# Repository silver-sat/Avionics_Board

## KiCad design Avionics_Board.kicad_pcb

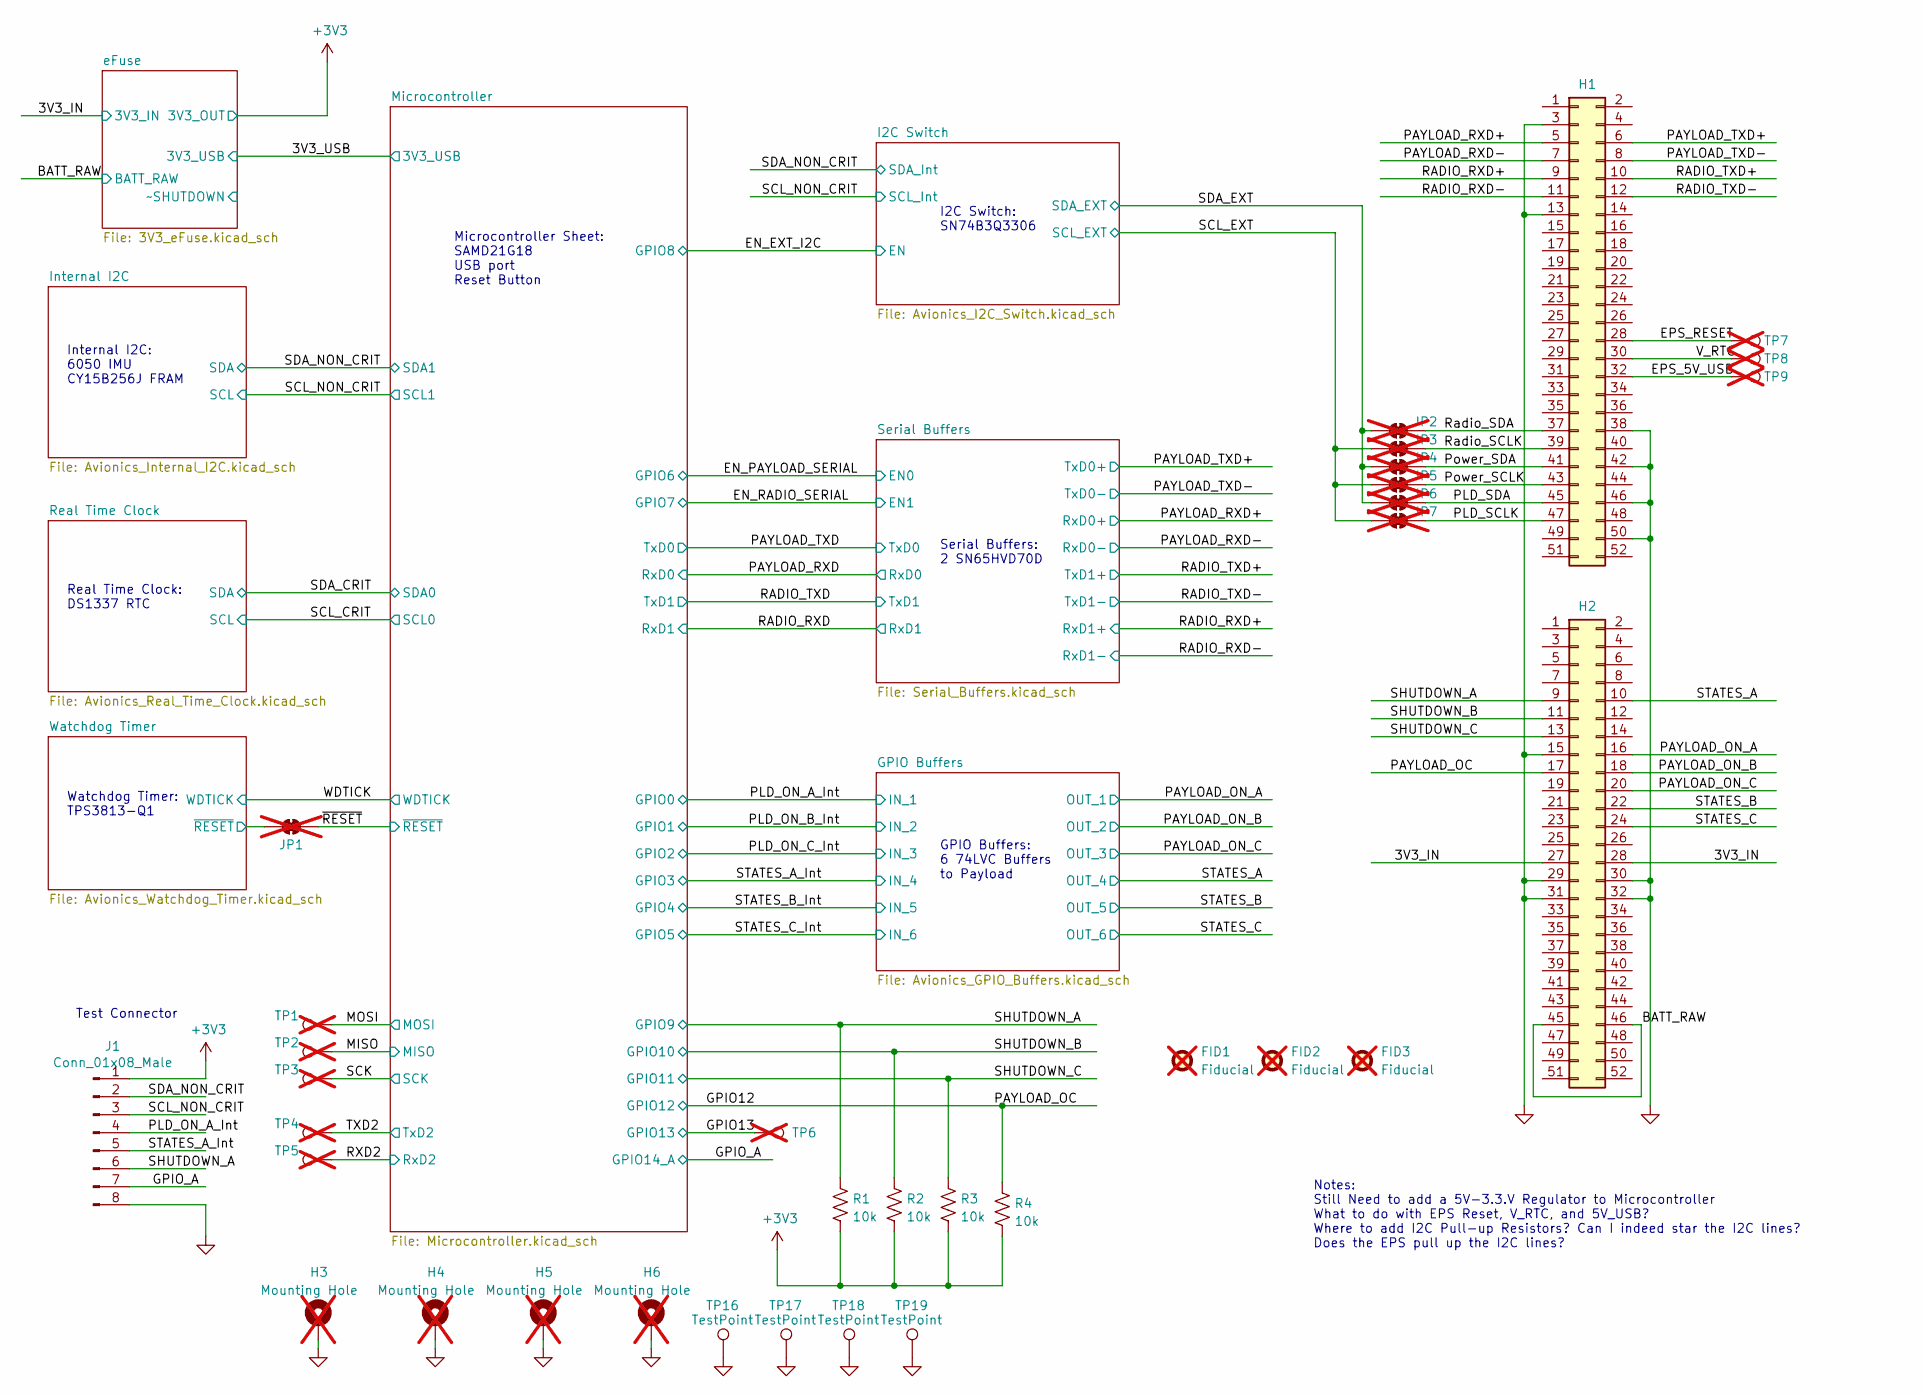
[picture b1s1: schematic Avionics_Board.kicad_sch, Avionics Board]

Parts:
FID1, FID2, FID3: Fiducial; Fiducial_1.5mm_Mask2.5mm; not fitted
H1, H2: Conn_02x26_Odd_Even; TheBus2x26; Part_Number ESQ-126-37-G-D
H3, H4, H5, H6: Mounting Hole; MountingHole_3.2mm_M3_Pad; not fitted
J1: Conn_01x08_Male; PinHeader_1x08_P2.54mm_Vertical; MPN TSW-108-26-L-S
JP1, JP2, JP3, JP4, JP5, JP6, JP7: SolderJumper_2_Bridged; SolderJumper-2_P1.3mm_Open_RoundedPad1.0x1.5mm; not fitted
R1, R2, R3, R4: 10k; R_0603_1608Metric; Part_Number ERJ-3EKF1002V
TP1: MOSI; TestPoint_Pad_2.0x2.0mm; not fitted
TP2: MISO; TestPoint_Pad_2.0x2.0mm; not fitted
TP3: SCK; TestPoint_Pad_2.0x2.0mm; not fitted
TP4: TXD2; TestPoint_Pad_2.0x2.0mm; not fitted
TP5: RXD2; TestPoint_Pad_2.0x2.0mm; not fitted
TP6: GPIO13; TestPoint_Pad_2.0x2.0mm; not fitted
TP7: EPS_RESET; TestPoint_Pad_2.0x2.0mm; not fitted
TP8: V_RTC; TestPoint_Pad_2.0x2.0mm; not fitted
TP9: EPS_5V_USB; TestPoint_Pad_2.0x2.0mm; not fitted
TP16, TP17, TP18, TP19: TestPoint; TestPoint_Keystone_5019_Minature; MPN 5019

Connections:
+3V3: J1.1, R1.2, R2.2, R3.2, R4.2; also elsewhere on the board
/3V3_IN: H2.27, H2.28; also elsewhere on the board
/BATT_RAW: H2.45, H2.46; also elsewhere on the board
/EPS_5V_USB: H1.32, TP9.1
/EPS_RESET: H1.28, TP7.1
/GPIO12: H2.17, R4.1; also elsewhere on the board
/GPIO13: TP6.1; also elsewhere on the board
/GPIO_A: J1.7; also elsewhere on the board
/MISO: TP2.1; also elsewhere on the board
/MOSI: TP1.1; also elsewhere on the board
/PAYLOAD_ON_A: H2.16; also elsewhere on the board
/PAYLOAD_ON_B: H2.18; also elsewhere on the board
/PAYLOAD_ON_C: H2.20; also elsewhere on the board
/PAYLOAD_RXD+: H1.5; also elsewhere on the board
/PAYLOAD_RXD-: H1.7; also elsewhere on the board
/PAYLOAD_TXD+: H1.6; also elsewhere on the board
/PAYLOAD_TXD-: H1.8; also elsewhere on the board
/PLD_ON_A_Int: J1.4; also elsewhere on the board
/PLD_SCLK: H1.47, JP7.2 (B)
/PLD_SDA: H1.45, JP6.2 (B)
/Power_SCLK: H1.43, JP5.2 (B)
/Power_SDA: H1.41, JP4.2 (B)
/RADIO_RXD+: H1.9; also elsewhere on the board
/RADIO_RXD-: H1.11; also elsewhere on the board
/RADIO_TXD+: H1.10; also elsewhere on the board
/RADIO_TXD-: H1.12; also elsewhere on the board
/RXD2: TP5.1; also elsewhere on the board
/Radio_SCLK: H1.39, JP3.2 (B)
/Radio_SDA: H1.37, JP2.2 (B)
/SCK: TP3.1; also elsewhere on the board
/SCL_EXT: JP3.1 (A), JP5.1 (A), JP7.1 (A); also elsewhere on the board
/SCL_NON_CRIT: J1.3; also elsewhere on the board
/SDA_EXT: JP2.1 (A), JP4.1 (A), JP6.1 (A); also elsewhere on the board
/SDA_NON_CRIT: J1.2; also elsewhere on the board
/SHUTDOWN_A: H2.9, J1.6, R1.1; also elsewhere on the board
/SHUTDOWN_B: H2.11, R2.1; also elsewhere on the board
/SHUTDOWN_C: H2.13, R3.1; also elsewhere on the board
/STATES_A: H2.10; also elsewhere on the board
/STATES_A_Int: J1.5; also elsewhere on the board
/STATES_B: H2.22; also elsewhere on the board
/STATES_C: H2.24; also elsewhere on the board
/TXD2: TP4.1; also elsewhere on the board
/V_RTC: H1.30, TP8.1
/Watchdog Timer/~RESET: JP1.1 (A); also elsewhere on the board
/~RESET: JP1.2 (B); also elsewhere on the board
GND: H1.3, H1.13, H1.38, H1.42, H1.46, H1.50, H2.15, H2.29, H2.30, H2.31, H2.32, H3.1, H4.1, H5.1, H6.1, J1.8, TP16.1, TP17.1, TP18.1, TP19.1; also elsewhere on the board

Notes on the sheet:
GPIO Buffers: 6 74LVC Buffers to Payload
Serial Buffers: 2 SN65HVD70D
Watchdog Timer: TPS3813-Q1
Real Time Clock: DS1337 RTC
Microcontroller Sheet: SAMD21G18 USB port Reset Button
Notes: Still Need to add a 5V-3.3.V Regulator to Microcontroller What to do with EPS Reset, V_RTC, and 5V_USB? Where to add I2C Pull-up Resistors? Can I indeed star the I2C lines? Does the EPS pull up the I2C lines?
Internal I2C: 6050 IMU CY15B256J FRAM
I2C Switch: SN74B3Q3306
Test Connector

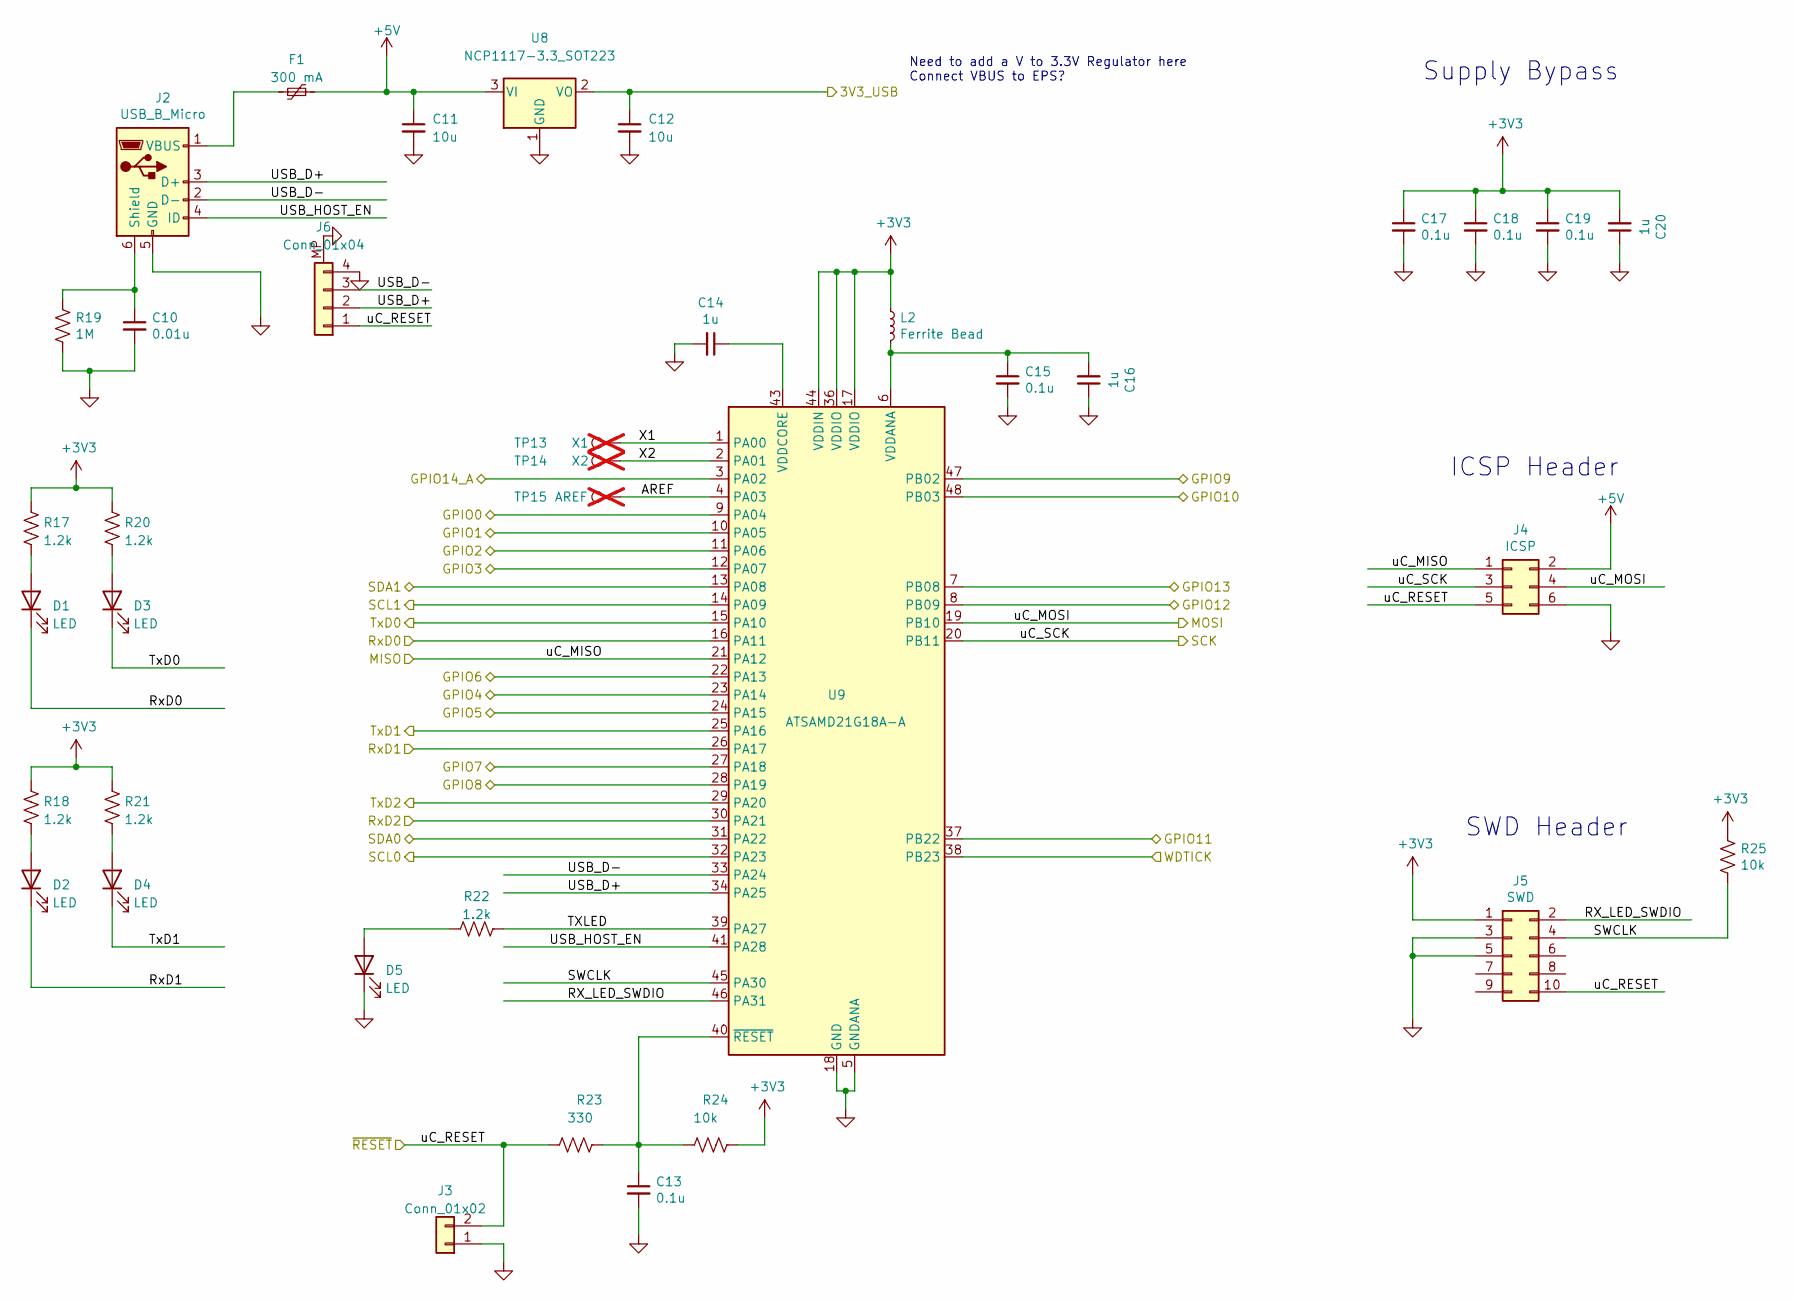
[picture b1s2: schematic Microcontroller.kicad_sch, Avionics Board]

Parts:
C10: 0.01u; C_0603_1608Metric; Part_Number 06035C472K4Z2A
C11, C12: 10u; C_2220_5650Metric_Pad1.97x5.40mm_HandSolder; Part_Number 22205C106K4Z4A
C13, C15, C17, C18, C19: 0.1u; C_0603_1608Metric; Part_Number 06035C104K4Z2A
C14, C16, C20: 1u; C_1206_3216Metric; Part_Number 12065C105M4Z2A
D1, D2, D3, D4, D5: LED; LED_0603_1608Metric; MPN CSL0903UT1C
F1: 300 mA; Fuse_0805_2012Metric; Part_Number PICOASMDC012S-2
J2: USB_B_Micro; USB_Micro-B_Molex-105017-0001; Part_Number 105017-0001
J3: Conn_01x02; PinHeader_1x02_P2.54mm_Vertical; MPN TSW-102-26-L-S
J4: ICSP; PinHeader_2x03_P2.54mm_Vertical; MPN MTSW-103-06-G-D-110
J5: SWD; PinHeader_2x05_P1.27mm_Vertical_SMD; Part_Number 4048
J6: Conn_01x04; Molex_PicoBlade_53261-0471_1x04-1MP_P1.25mm_Horizontal; MPN 53261-0471
L2: Ferrite Bead; L_0603_1608Metric; Part_Number BLM18SP102SH1D
R17, R18, R20, R21, R22: 1.2k; R_0603_1608Metric; Part_Number ERJ-3EKF9310V
R19: 1M; R_0603_1608Metric; Part_Number ERJ-3EKF1004V
R23: 330; R_0603_1608Metric; Part_Number ERJ-3EKF3300V
R24, R25: 10k; R_0603_1608Metric; Part_Number ERJ-3EKF1002V
TP13: X1; TestPoint_Pad_2.0x2.0mm; not fitted
TP14: X2; TestPoint_Pad_2.0x2.0mm; not fitted
TP15: AREF; TestPoint_Pad_2.0x2.0mm; not fitted
U8: NCP1117-3.3_SOT223; SOT-223-3_TabPin2; Part_Number NCP1117
U9: ATSAMD21G18A-A; TQFP-48_7x7mm_P0.5mm; Part_Number ATSAMD21G18A-AF

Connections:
+3V3: C17.1, C18.1, C19.1, C20.2, J5.1, L2.1, R17.1, R18.1, R20.1, R21.1, R24.1, R25.1, U9.17 (VDDIO), U9.36 (VDDIO), U9.44 (VDDIN); also elsewhere on the board
+5V: C11.1, F1.2, J4.2, U8.3 (VI)
/3V3_USB: C12.1, U8.2 (VO); also elsewhere on the board
/EN_EXT_I2C: U9.28 (PA19); also elsewhere on the board
/EN_PAYLOAD_SERIAL: U9.22 (PA13); also elsewhere on the board
/EN_RADIO_SERIAL: U9.27 (PA18); also elsewhere on the board
/GPIO12: U9.8 (PB09); also elsewhere on the board
/GPIO13: U9.7 (PB08); also elsewhere on the board
/GPIO_A: U9.3 (PA02); also elsewhere on the board
/MISO: J4.1, U9.21 (PA12); also elsewhere on the board
/MOSI: J4.4, U9.19 (PB10); also elsewhere on the board
/Microcontroller/AREF: TP15.1, U9.4 (PA03)
/Microcontroller/RX_LED_SWDIO: J5.2, U9.46 (PA31)
/Microcontroller/SWCLK: J5.4, R25.2, U9.45 (PA30)
/Microcontroller/TXLED: R22.2, U9.39 (PA27)
/Microcontroller/USB_D+: J2.3 (D+), J6.2, U9.34 (PA25)
/Microcontroller/USB_D-: J2.2 (D-), J6.3, U9.33 (PA24)
/Microcontroller/USB_HOST_EN: J2.4 (ID), U9.41 (PA28)
/Microcontroller/X1: TP13.1, U9.1 (PA00)
/Microcontroller/X2: TP14.1, U9.2 (PA01)
/PAYLOAD_RXD: D1.1 (K), U9.16 (PA11); also elsewhere on the board
/PAYLOAD_TXD: D3.1 (K), U9.15 (PA10); also elsewhere on the board
/PLD_ON_A_Int: U9.9 (PA04); also elsewhere on the board
/PLD_ON_B_Int: U9.10 (PA05); also elsewhere on the board
/PLD_ON_C_Int: U9.11 (PA06); also elsewhere on the board
/RADIO_RXD: D2.1 (K), U9.26 (PA17); also elsewhere on the board
/RADIO_TXD: D4.1 (K), U9.25 (PA16); also elsewhere on the board
/RXD2: U9.30 (PA21); also elsewhere on the board
/SCK: J4.3, U9.20 (PB11); also elsewhere on the board
/SCL_CRIT: U9.32 (PA23); also elsewhere on the board
/SCL_NON_CRIT: U9.14 (PA09); also elsewhere on the board
/SDA_CRIT: U9.31 (PA22); also elsewhere on the board
/SDA_NON_CRIT: U9.13 (PA08); also elsewhere on the board
/SHUTDOWN_A: U9.47 (PB02); also elsewhere on the board
/SHUTDOWN_B: U9.48 (PB03); also elsewhere on the board
/SHUTDOWN_C: U9.37 (PB22); also elsewhere on the board
/STATES_A_Int: U9.12 (PA07); also elsewhere on the board
/STATES_B_Int: U9.23 (PA14); also elsewhere on the board
/STATES_C_Int: U9.24 (PA15); also elsewhere on the board
/TXD2: U9.29 (PA20); also elsewhere on the board
/WDTICK: U9.38 (PB23); also elsewhere on the board
/~RESET: J3.2, J4.5, J5.10, J6.1, R23.2; also elsewhere on the board
GND: C10.2, C11.2, C12.2, C13.2, C14.2, C15.2, C16.1, C17.2, C18.2, C19.2, C20.1, D5.1 (K), J2.5 (GND), J3.1, J4.6, J5.3, J5.5, J6.4, J6.MP, R19.2, U8.1 (GND), U9.5 (GNDANA), U9.18 (GND), U9.35 (GND), U9.42 (GND); also elsewhere on the board
unnamed: D1.2 (A), R17.2
unnamed: D2.2 (A), R18.2
unnamed: D3.2 (A), R20.2
unnamed: D4.2 (A), R21.2
unnamed: D5.2 (A), R22.1
unnamed: C10.1, J2.6 (Shield), R19.1
unnamed: F1.1, J2.1 (VBUS)
unnamed: C15.1, C16.2, L2.2, U9.6 (VDDANA)
unnamed: C14.1, U9.43 (VDDCORE)
unnamed: C13.1, R23.1, R24.2, U9.40 (~RESET)

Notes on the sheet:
Need to add a V to 3.3V Regulator here Connect VBUS to EPS?
ICSP Header
SWD Header
Supply Bypass

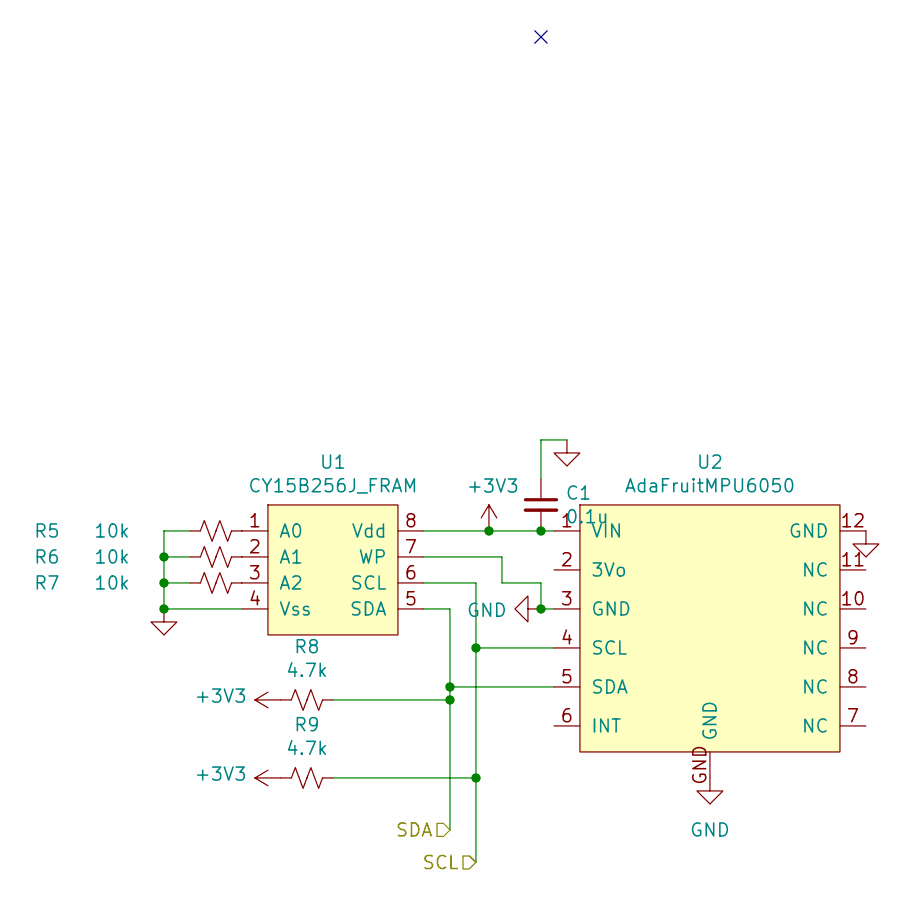
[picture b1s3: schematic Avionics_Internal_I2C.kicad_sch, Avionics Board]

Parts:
C1: 0.1u; C_0603_1608Metric; Part_Number 06035C104K4Z2A
R5, R6, R7: 10k; R_0603_1608Metric; Part_Number ERJ-3EKF1002V
R8, R9: 4.7k; R_0603_1608Metric; Part_Number ERJ-3EKF4701V
U1: CY15B256J_FRAM; SOP-8_5.28x5.23mm_P1.27mm; Part_Number CY15B256J
U2: AdaFruitMPU6050; MPU_6050; Part_Number MPU6050

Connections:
+3V3: C1.2, R8.2, R9.2, U1.8 (Vdd), U2.1 (VIN); also elsewhere on the board
/SCL_NON_CRIT: R9.1, U1.6 (SCL), U2.4 (SCL); also elsewhere on the board
/SDA_NON_CRIT: R8.1, U1.5 (SDA), U2.5 (SDA); also elsewhere on the board
GND: C1.1, R5.2, R6.2, R7.2, U1.4 (Vss), U1.7 (WP), U2.3 (GND), U2.12 (GND), U2.GND; also elsewhere on the board
unnamed: R5.1, U1.1 (A0)
unnamed: R6.1, U1.2 (A1)
unnamed: R7.1, U1.3 (A2)

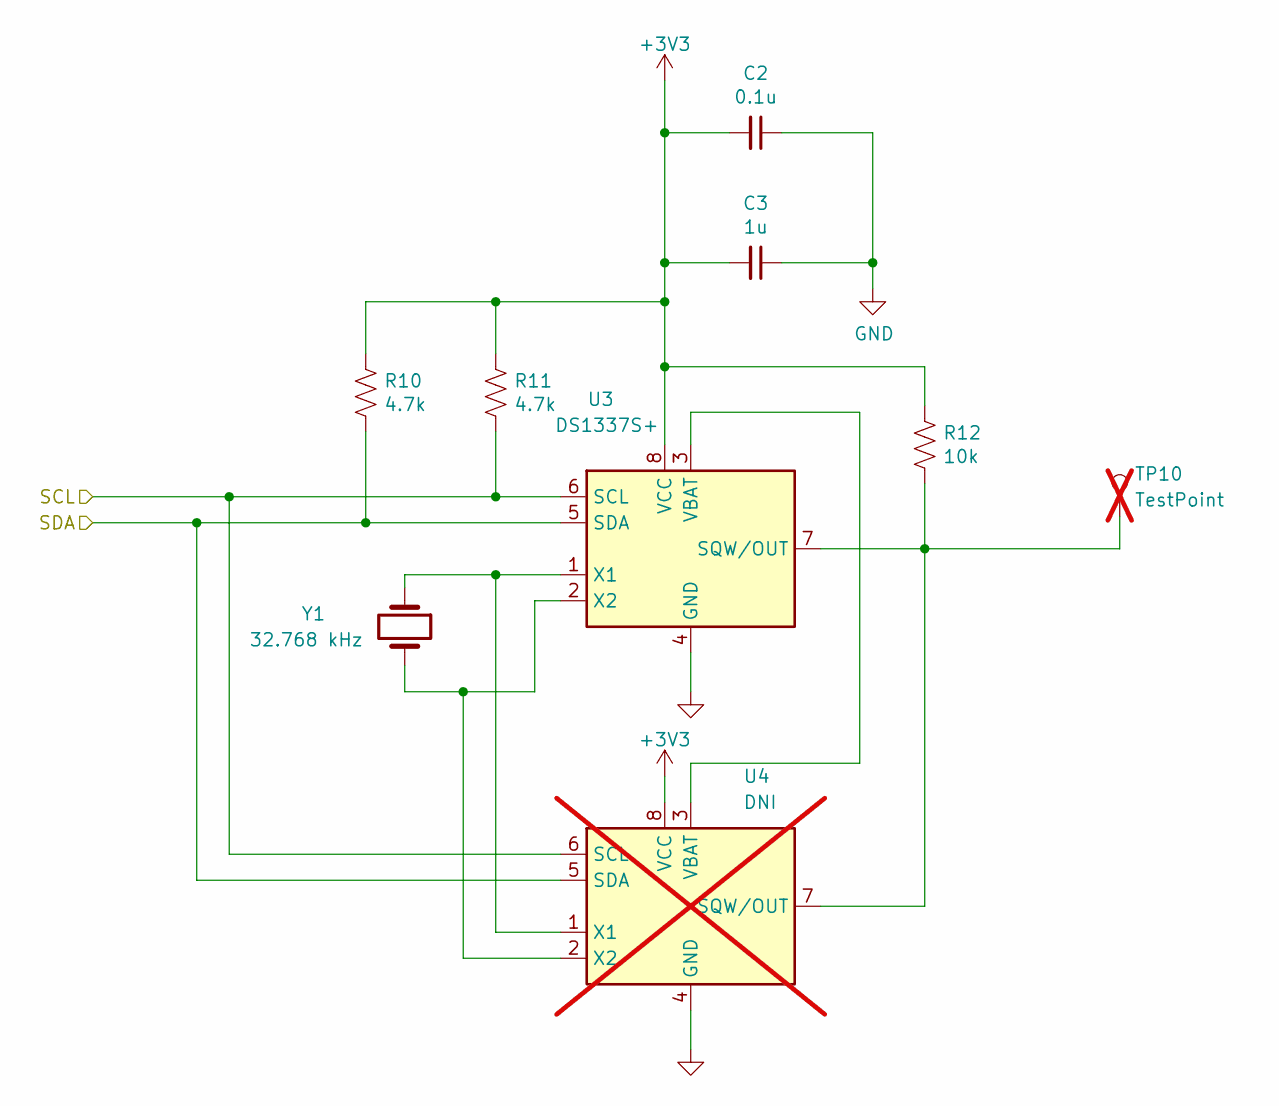
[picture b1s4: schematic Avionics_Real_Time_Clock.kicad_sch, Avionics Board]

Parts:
C2: 0.1u; C_0603_1608Metric; Part_Number 06035C104K4Z2A
C3: 1u; C_1206_3216Metric; Part_Number 12065C105M4Z2A
R10, R11: 4.7k; R_0603_1608Metric; Part_Number ERJ-3EKF4701V
R12: 10k; R_0603_1608Metric; Part_Number ERJ-3EKF1002V
TP10: TestPoint; TestPoint_Pad_2.0x2.0mm; not fitted
U3: DS1337S+; SOIC-8_3.9x4.9mm_P1.27mm; Part_Number DS1337S+T&R
U4: DNI; DIP-8_W7.62mm; Part_Number DS1337+; not fitted
Y1: 32.768 kHz; Crystal_SMD_3215-2Pin_3.2x1.5mm; Part_Number ECS-.327-6-34QCS-TR

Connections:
+3V3: C2.2, C3.2, R10.1, R11.1, R12.1, U3.8 (VCC), U4.8 (VCC); also elsewhere on the board
/SCL_CRIT: R11.2, U3.6 (SCL), U4.6 (SCL); also elsewhere on the board
/SDA_CRIT: R10.2, U3.5 (SDA), U4.5 (SDA); also elsewhere on the board
GND: C2.1, C3.1, U3.4 (GND), U4.4 (GND); also elsewhere on the board
unnamed: R12.2, TP10.1, U3.7 (SQW/OUT), U4.7 (SQW/OUT)
unnamed: U3.3 (VBAT), U4.3 (VBAT)
unnamed: U3.1 (X1), U4.1 (X1), Y1.1
unnamed: U3.2 (X2), U4.2 (X2), Y1.2

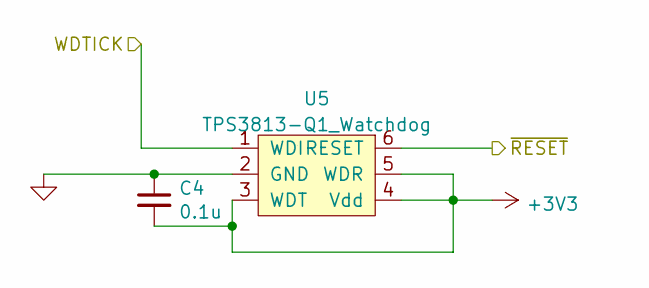
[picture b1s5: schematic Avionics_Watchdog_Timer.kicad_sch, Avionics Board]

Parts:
C4: 0.1u; C_0603_1608Metric; Part_Number 06035C104K4Z2A
U5: TPS3813-Q1_Watchdog; SOT-23-6; Part_Number TPS3813I50QDBVRQ1

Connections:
+3V3: C4.2, U5.3 (WDT), U5.4 (Vdd), U5.5 (WDR); also elsewhere on the board
/WDTICK: U5.1 (WDI); also elsewhere on the board
/Watchdog Timer/~RESET: U5.6 (RESET); also elsewhere on the board
GND: C4.1, U5.2 (GND); also elsewhere on the board

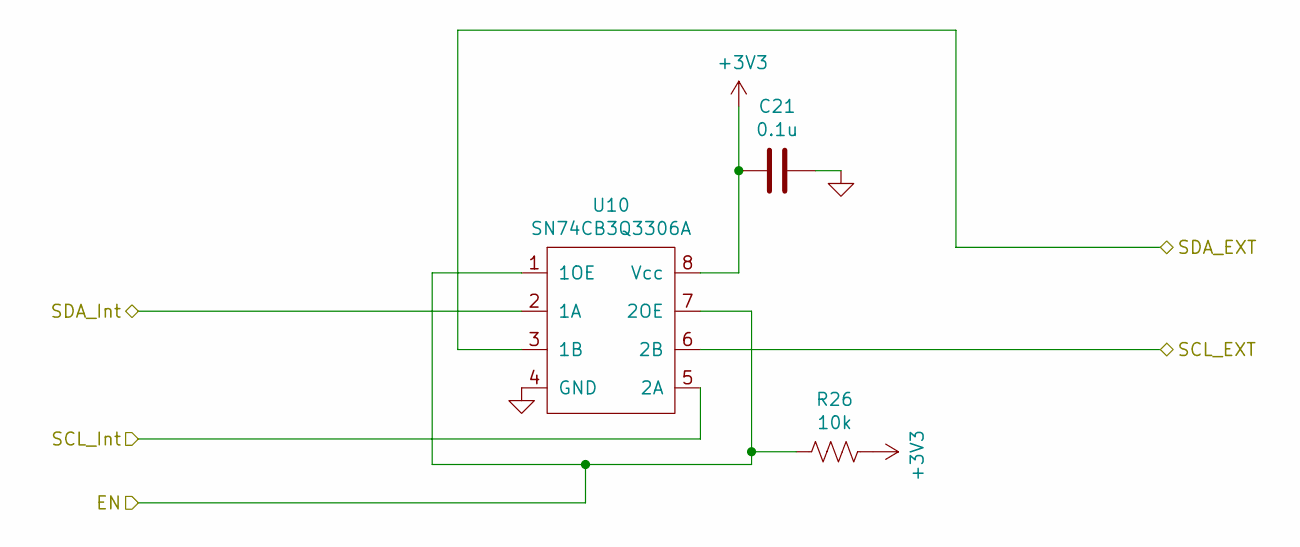
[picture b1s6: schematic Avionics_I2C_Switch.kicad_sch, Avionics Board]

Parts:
C21: 0.1u; C_0603_1608Metric; Part_Number 06035C104K4Z2A
R26: 10k; R_0603_1608Metric; Part_Number ERJ-3EKF1002V
U10: SN74CB3Q3306A; TSSOP-8_4.4x3mm_P0.65mm; Part_Number SN74CB3Q3306A

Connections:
+3V3: C21.1, R26.1, U10.8 (Vcc); also elsewhere on the board
/EN_EXT_I2C: R26.2, U10.1 (1OE), U10.7 (2OE); also elsewhere on the board
/SCL_EXT: U10.6 (2B); also elsewhere on the board
/SCL_NON_CRIT: U10.5 (2A); also elsewhere on the board
/SDA_EXT: U10.3 (1B); also elsewhere on the board
/SDA_NON_CRIT: U10.2 (1A); also elsewhere on the board
GND: C21.2, U10.4 (GND); also elsewhere on the board

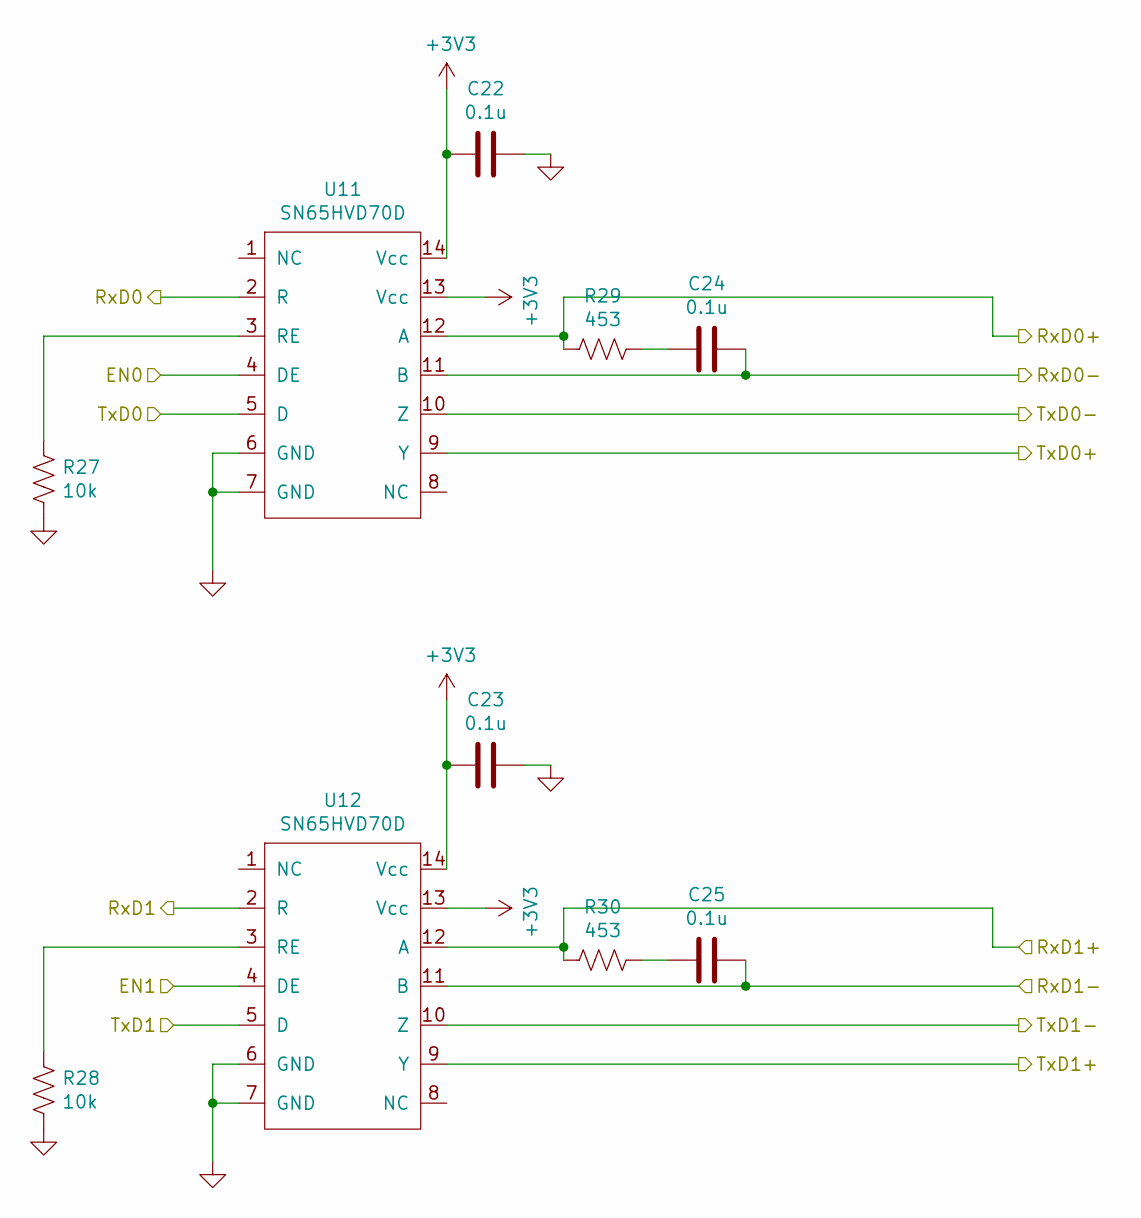
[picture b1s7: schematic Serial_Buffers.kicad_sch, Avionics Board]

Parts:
C22, C23, C24, C25: 0.1u; C_0603_1608Metric; Part_Number 06035C104K4Z2A
R27, R28: 10k; R_0603_1608Metric; Part_Number ERJ-3EKF1002V
R29, R30: 453; R_0603_1608Metric; Part_Number ERJ-3EKF4530V
U11, U12: SN65HVD70D; SOIC-14_3.9x8.7mm_P1.27mm; Part_Number SN65HVD70D

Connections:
+3V3: C22.1, C23.1, U11.13 (Vcc), U11.14 (Vcc), U12.13 (Vcc), U12.14 (Vcc); also elsewhere on the board
/EN_PAYLOAD_SERIAL: U11.4 (DE); also elsewhere on the board
/EN_RADIO_SERIAL: U12.4 (DE); also elsewhere on the board
/PAYLOAD_RXD: U11.2 (R); also elsewhere on the board
/PAYLOAD_RXD+: R29.2, U11.12 (A); also elsewhere on the board
/PAYLOAD_RXD-: C24.2, U11.11 (B); also elsewhere on the board
/PAYLOAD_TXD: U11.5 (D); also elsewhere on the board
/PAYLOAD_TXD+: U11.9 (Y); also elsewhere on the board
/PAYLOAD_TXD-: U11.10 (Z); also elsewhere on the board
/RADIO_RXD: U12.2 (R); also elsewhere on the board
/RADIO_RXD+: R30.2, U12.12 (A); also elsewhere on the board
/RADIO_RXD-: C25.2, U12.11 (B); also elsewhere on the board
/RADIO_TXD: U12.5 (D); also elsewhere on the board
/RADIO_TXD+: U12.9 (Y); also elsewhere on the board
/RADIO_TXD-: U12.10 (Z); also elsewhere on the board
GND: C22.2, C23.2, R27.2, R28.2, U11.6 (GND), U11.7 (GND), U12.6 (GND), U12.7 (GND); also elsewhere on the board
unnamed: C24.1, R29.1
unnamed: C25.1, R30.1
unnamed: R27.1, U11.3 (RE)
unnamed: R28.1, U12.3 (RE)

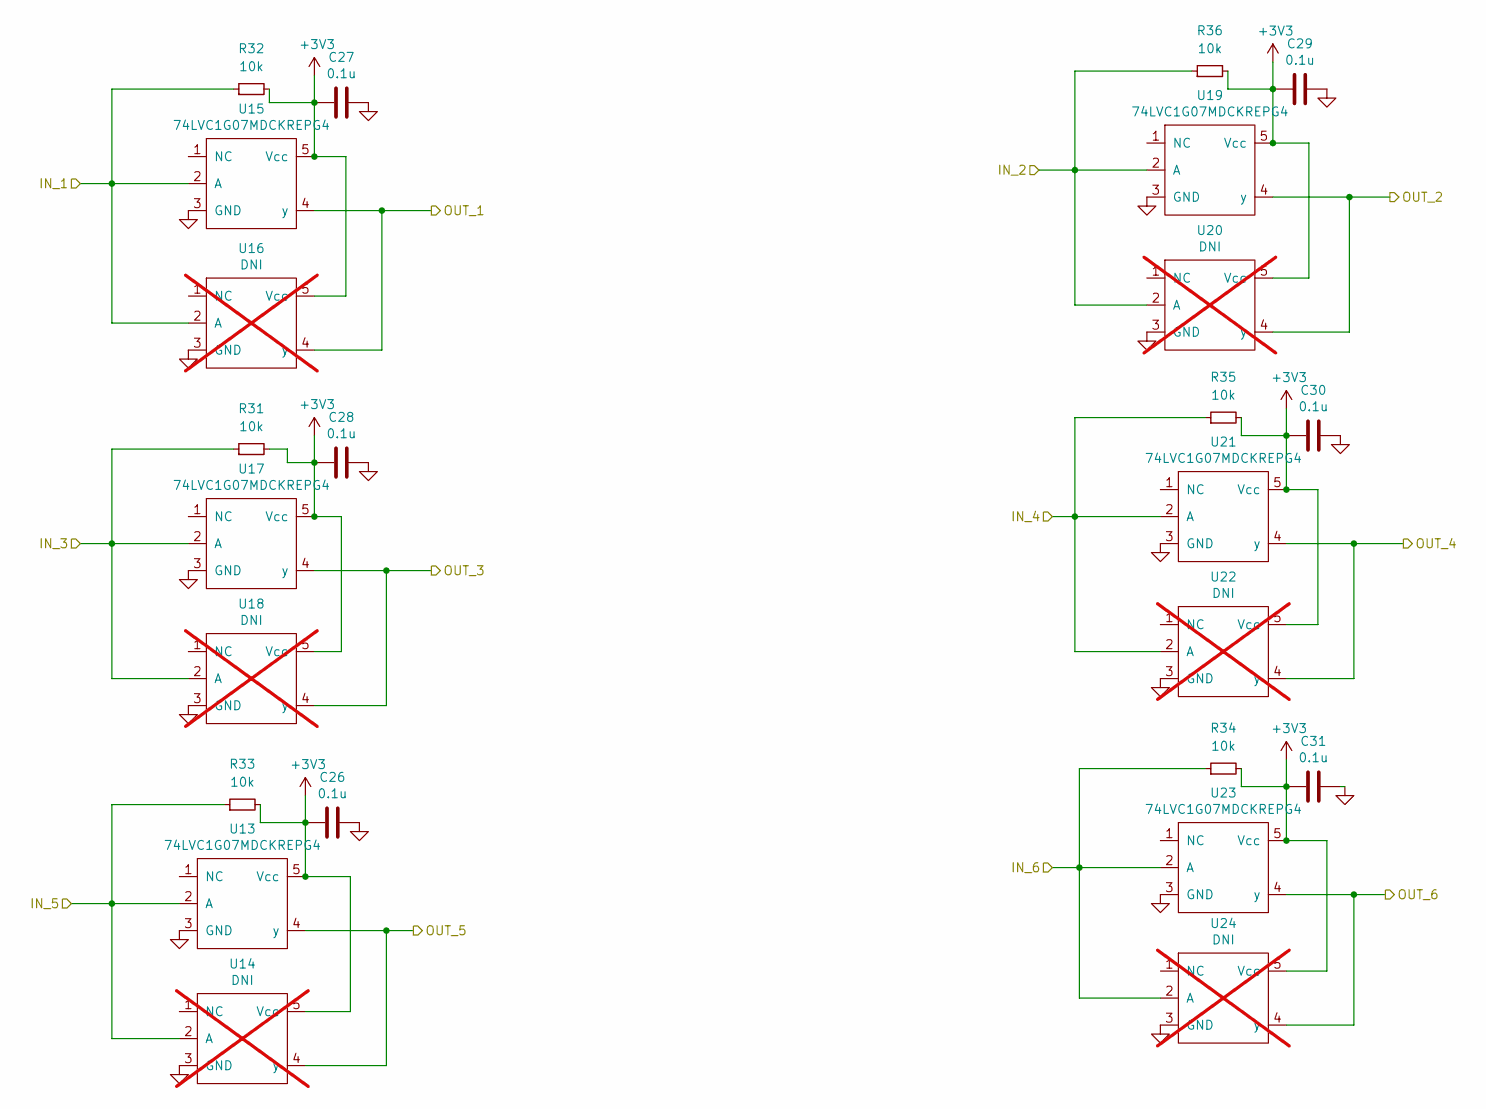
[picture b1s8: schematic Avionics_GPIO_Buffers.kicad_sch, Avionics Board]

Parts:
C26, C27, C28, C29, C30, C31: 0.1u; C_0603_1608Metric; Part_Number 06035C104K4Z2A
R31, R32, R33, R34, R35, R36: 10k; R_0603_1608Metric; MPN ERJ-3RBD1002V
U13, U15, U17, U19, U21, U23: 74LVC1G07MDCKREPG4; SOT-353_SC-70-5; Part_Number 74LVC1G07MDCKREPG4
U14, U16, U18, U20, U22, U24: DNI; SOT-23-5; not fitted

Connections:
+3V3: C26.2, C27.2, C28.2, C29.2, C30.2, C31.2, R31.2, R32.2, R33.2, R34.2, R35.2, R36.2, U13.5 (Vcc), U14.5 (Vcc), U15.5 (Vcc), U16.5 (Vcc), U17.5 (Vcc), U18.5 (Vcc), U19.5 (Vcc), U20.5 (Vcc), U21.5 (Vcc), U22.5 (Vcc), U23.5 (Vcc), U24.5 (Vcc); also elsewhere on the board
/PAYLOAD_ON_A: U15.4 (y), U16.4 (y); also elsewhere on the board
/PAYLOAD_ON_B: U19.4 (y), U20.4 (y); also elsewhere on the board
/PAYLOAD_ON_C: U17.4 (y), U18.4 (y); also elsewhere on the board
/PLD_ON_A_Int: R32.1, U15.2 (A), U16.2 (A); also elsewhere on the board
/PLD_ON_B_Int: R36.1, U19.2 (A), U20.2 (A); also elsewhere on the board
/PLD_ON_C_Int: R31.1, U17.2 (A), U18.2 (A); also elsewhere on the board
/STATES_A: U21.4 (y), U22.4 (y); also elsewhere on the board
/STATES_A_Int: R35.1, U21.2 (A), U22.2 (A); also elsewhere on the board
/STATES_B: U13.4 (y), U14.4 (y); also elsewhere on the board
/STATES_B_Int: R33.1, U13.2 (A), U14.2 (A); also elsewhere on the board
/STATES_C: U23.4 (y), U24.4 (y); also elsewhere on the board
/STATES_C_Int: R34.1, U23.2 (A), U24.2 (A); also elsewhere on the board
GND: C26.1, C27.1, C28.1, C29.1, C30.1, C31.1, U13.3 (GND), U14.3 (GND), U15.3 (GND), U16.3 (GND), U17.3 (GND), U18.3 (GND), U19.3 (GND), U20.3 (GND), U21.3 (GND), U22.3 (GND), U23.3 (GND), U24.3 (GND); also elsewhere on the board

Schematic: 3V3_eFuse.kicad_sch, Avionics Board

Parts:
C5, C7, C8, C9, C32: 0.1u; C_0603_1608Metric; Part_Number 06035C104K4Z2A
C6: 10u; C_2220_5650Metric_Pad1.97x5.40mm_HandSolder; Part_Number 22205C106K4Z4A
C33: 10u; C_0603_1608Metric; Part_Number 22205C106K4Z4A
JP8, JP10: SolderJumper_2_Bridged; SolderJumper-2_P1.3mm_Bridged_RoundedPad1.0x1.5mm; not fitted
JP9: SolderJumper_2_Open; SolderJumper-2_P1.3mm_Open_TrianglePad1.0x1.5mm; not fitted
L1, L3: Ferrite Bead; L_0603_1608Metric; Part_Number BLM18SP102SH1D
R13, R14, R15, R16, R37: 10k; R_0603_1608Metric; Part_Number ERJ-3EKF1002V
TP11, TP12: TestPoint; TestPoint_Pad_2.0x2.0mm; not fitted
U6: FPF2000; SOT-353_SC-70-5; Part_Number FPF2000
U7: TPS2105MDBVREP; SOT-23-5; Part_Number TPS2105MDBVREP
U25: NCV8114ASN330T1G; TSOT-23-5; MPN NCV8114ASN330T1G

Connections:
+3V3: C9.1, TP12.1, U7.4 (OUT); also elsewhere on the board
/3V3_IN: C5.1, L1.1; also elsewhere on the board
/3V3_USB: U7.3 (IN2); also elsewhere on the board
/BATT_RAW: C32.1, L3.1; also elsewhere on the board
/eFuse/3V3_IN_FILT: C6.1, JP9.1 (A), L1.2, R13.1
/eFuse/~SHUTDOWN: R13.2, U6.4 (ON)
GND: C5.2, C6.2, C7.2, C8.2, C9.2, C32.2, C33.2, R16.2, U6.2 (GND), U7.2 (GND), U25.2 (GND); also elsewhere on the board
unnamed: C33.1, JP8.1 (A), L3.2
unnamed: JP8.2 (B), R37.1, U25.1 (IN)
unnamed: JP10.1 (A), U25.5 (OUT)
unnamed: JP9.2 (B), JP10.2 (B), R14.1, R15.1, U6.5 (VIN)
unnamed: R15.2, U6.3 (FLAGB)
unnamed: C7.1, C8.1, R16.1, TP11.1, U6.1 (VOUT), U7.5 (IN1)
unnamed: R14.2, U7.1 (EN)
unnamed: R37.2, U25.3 (EN)

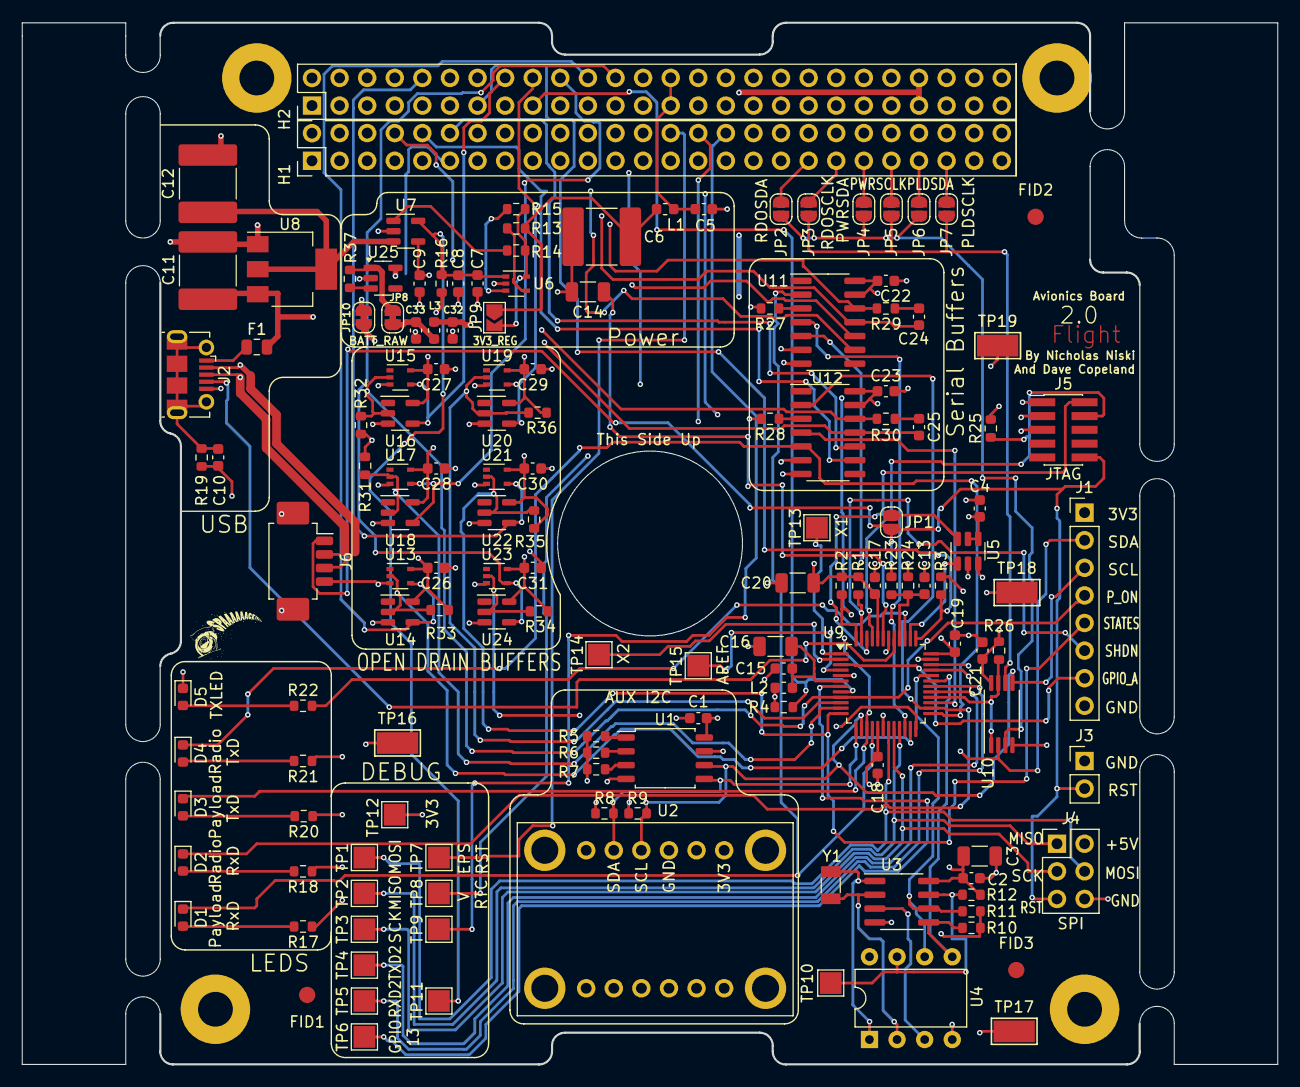
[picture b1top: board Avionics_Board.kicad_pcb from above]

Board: 4 copper layers, 115.6 x 95.9 mm, 149 parts (0 on the bottom side), 102 nets.
